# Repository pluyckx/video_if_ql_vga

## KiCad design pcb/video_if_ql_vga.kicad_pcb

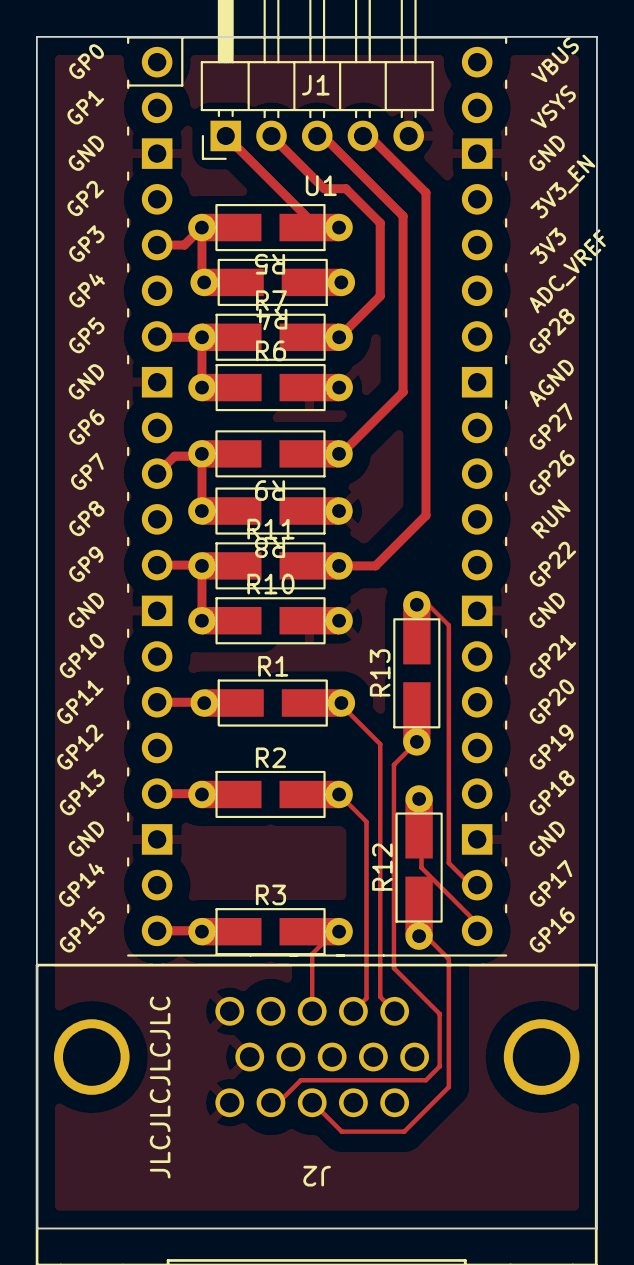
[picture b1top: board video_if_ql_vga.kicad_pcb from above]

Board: 2 copper layers, 31.1 x 66.2 mm, 16 parts (0 on the bottom side), 19 nets.

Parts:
J1: Conn_01x05; PinHeader_1x05_P2.54mm_Horizontal
J2: DB15_Female_HighDensity; CONN_L77HDE15SD1CH4FVGA_AMP
R1, R2, R3, R5, R7, R9, R11: 330R; R_Axial_DIN0207_L6.3mm_D2.5mm_P7.62_Horizontal
R4, R6, R8, R10: 680R; R_Axial_DIN0207_L6.3mm_D2.5mm_P7.62_Horizontal
R12, R13: 100R; R_Axial_DIN0207_L6.3mm_D2.5mm_P7.62_Horizontal
U1: SC0915; RPi_Pico_SMD_TH

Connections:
/BLUE: R3.1, U1.20 (GP15)
/GREEN: R2.1, U1.17 (GP13)
/HSYNC: R12.2, U1.21 (GP16)
/QLBLUE: R8.2, R9.2, U1.10 (GP7)
/QLGREEN: R6.1, R7.1, U1.7 (GP5)
/QLRED: R4.2, R5.2, U1.5 (GP3)
/QLSYNC: R10.1, R11.1, U1.12 (GP9)
/RED: R1.1, U1.15 (GP11)
/VSYNC: R13.2, U1.22 (GP17)
GND: J1.5, J2.5, J2.6, J2.7, J2.8, J2.10, J2.15, R4.1, R6.2, R8.1, R10.2, U1.3 (GND), U1.8 (GND), U1.13 (GND), U1.18 (GND), U1.23 (GND), U1.28 (GND), U1.38 (GND)
unnamed: J1.1, R5.1
unnamed: J1.2, R7.2
unnamed: J1.3, R9.1
unnamed: J1.4, R11.2
unnamed: J2.1, R1.2
unnamed: J2.2, R2.2
unnamed: J2.3, R3.2
unnamed: J2.13, R12.1
unnamed: J2.14, R13.1

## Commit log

2023-04-14 Provide THT combined with SMD footprints for resistors
2023-05-19 Fix mistake in voltage divider
2023-05-19 Add smd footprints for resistors
